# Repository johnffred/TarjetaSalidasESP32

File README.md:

# 🔌 Proyecto: Tarjeta de salidas con ESP32

Este proyecto consiste en el diseño y desarrollo de una tarjeta electrónica basada en ESP32, que permite controlar múltiples salidas mediante relés de estado sólido, visualizar información en una pantalla LCD y recibir entradas desde botones físicos. Todo el diseño de hardware se ha realizado en **KiCad**.

---

## 📦 Componentes principales

| Componente             | Descripción                                      |
|------------------------|--------------------------------------------------|
| ESP32-WROOM-32D        | Microcontrolador principal                       |
| Relés G3MB-202P        | Relés de estado sólido para controlar salidas    |
| Pantalla LCD 16x2 I2C  | Interfaz de usuario                              |
| Botones de entrada     | Para control manual de salidas                   |
| Fuente IRM-05-5        | Fuente de 5 V conmutada                           |
| CH340C                 | Conversor USB a serial para programar el ESP32   |
| USB Tipo A             | Conexión de energía o programación               |

---

## 📐 Diseño en KiCad

- `esquematico.kicad_sch`: esquema eléctrico completo
- `pcb_layout.kicad_pcb`: diseño de la placa (en desarrollo)
- `BOM.csv`: lista de materiales (opcional)

---

## 💻 Programación

La programación se realiza en Arduino IDE o PlatformIO.  
Funcionalidades previstas:
- Activación de salidas mediante botones
- Visualización del estado de salidas en la pantalla LCD
- Control de pines y lógica de relés

📌 Asignación de pines:

| Función     | Pin ESP32 |
|-------------|-----------|
| Relé 1      | GPIO25    |
| Relé 2      | GPIO26    |
| Relé 3      | GPIO27    |
| Relé 4      | GPIO32    |
| Botones     | GPIO34, 35, 36, 39 |
| LCD I2C SDA | GPIO21    |
| LCD I2C SCL | GPIO22    |

---

## 📋 Estado del proyecto

| Tarea                          | Estado     |
|-------------------------------|------------|
| Diseño de esquema             | ✅ Completo |
| Diseño PCB                    | ⏳ En progreso |
| Programación básica           | ⏳ En pruebas |
| Pruebas de relés              | 🔜 Por hacer |
| Documentación en GitHub       | ✅ Lista    |

---

## 🧑‍💻 Autor

**John Franco**  
📅 Junio 2025  
🔗 Licencia: MIT

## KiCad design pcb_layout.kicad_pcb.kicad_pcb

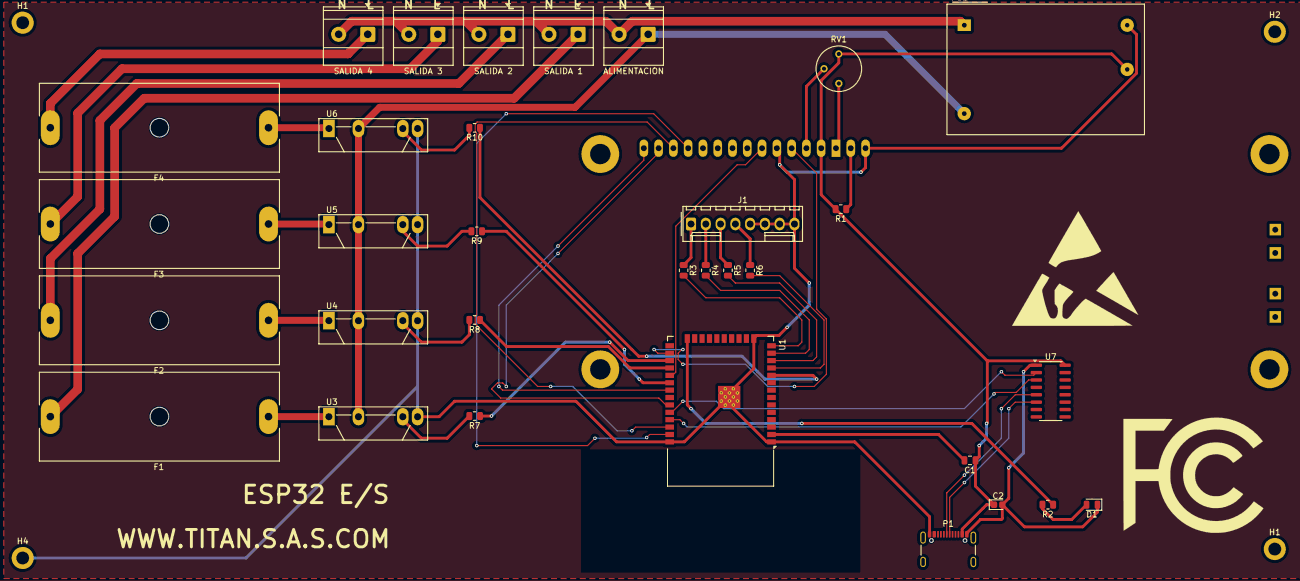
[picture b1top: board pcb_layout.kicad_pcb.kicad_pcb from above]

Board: 2 copper layers, 37 parts (1 on the bottom side), 43 nets.

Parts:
ALIMENTACION: alimentacion; TerminalBlock_Phoenix_MKDS-1,5-2_1x02_P5.00mm_Horizontal
C1: C100nF; C_0805_2012Metric
C2: C_Polarized; CP_EIA-1608-08_AVX-J
D1: LED; LED_0805_2012Metric
F1, F2, F3, F4: Fuse_Small; Fuseholder_Cylinder-6.3x32mm_Schurter_0031-8002_Horizontal_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
H1, H1#2, H2, H4: MountingHole_2.2mm_M2_DIN965_Pad
J1: Conn_01x08; Molex_KK-254_AE-6410-08A_1x08_P2.54mm_Vertical
P1: USB_C_Plug_USB2.0; USB_C_Receptacle_GCT_USB4105-xx-A_16P_TopMnt_Horizontal
PS1: IRM-02-5; Converter_ACDC_MeanWell_IRM-02-xx_THT
R1: R_US330ohn; R_0805_2012Metric
R2, R3, R4, R5, R6: R_US; R_0805_2012Metric
R7, R8, R9, R10: 330ohm; R_0805_2012Metric
RV1: R_Potentiometer_US; Potentiometer_Bourns_3339P_Vertical
SALIDA 1, SALIDA 2, SALIDA 3, SALIDA 4: salida; TerminalBlock_Phoenix_MKDS-1,5-2_1x02_P5.00mm_Horizontal
U1: ESP32-WROOM-32D
U2: LCD-016N002L
U3, U4, U5, U6: S202S02; SIP4_Sharp-SSR_P7.62mm_Straight
U7: CH340C; SOIC-16_3.9x9.9mm_P1.27mm

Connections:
IO01: U1.35 (TXD0/IO1), U7.3 (RXD)
IO03: U1.34 (RXD0/IO3), U7.2 (TXD)
IO4: U1.26 (IO4), U2.4 (RS)
IO5: U1.29 (IO5), U2.6 (E)
IO12: R3.2, U1.14 (IO12)
IO14: R4.2, U1.13 (IO14)
IO16: R7.1, U1.27 (IO16)
IO17: R8.1, U1.28 (IO17)
IO18: R9.1, U1.30 (IO18)
IO19: U1.31 (IO19), U2.14 (DB7)
IO21: U1.33 (IO21), U2.13 (DB6)
IO22: U1.36 (IO22), U2.12 (DB5)
IO23: U1.37 (IO23), U2.11 (DB4)
IO25: R10.1, U1.10 (IO25)
IO26: R6.2, U1.11 (IO26)
IO27: R5.2, U1.12 (IO27)
unnamed: D1.2 (A), R2.2
unnamed: F1.1, U3.1
unnamed: F2.1, U4.1
unnamed: F3.1, U5.1
unnamed: F4.1, U6.1
unnamed: J1.1, R3.1
unnamed: J1.2, R4.1
unnamed: J1.3, R5.1
unnamed: J1.4, R6.1
unnamed: F1.2, SALIDA 1.1
unnamed: F2.2, SALIDA 2.1
unnamed: F3.2, SALIDA 3.1
unnamed: F4.2, SALIDA 4.1
unnamed: P1.A6 (D+), U7.5 (UD+)
unnamed: P1.A7 (D-), U7.6 (UD-)
unnamed: R7.2, U3.3
unnamed: R8.2, U4.3
unnamed: R9.2, U5.3
unnamed: R10.2, U6.3
unnamed: R2.1, U1.24 (IO2)
unnamed: C1.2, U1.2 (VDD)
unnamed: R1.1, U2.15 (A/VEE)
unnamed: RV1.2, U2.3 (VO)
Neutro: ALIMENTACION.2, PS1.1 (AC/N), SALIDA 1.2, SALIDA 2.2, SALIDA 3.2, SALIDA 4.2
gnd: C2.2, D1.1 (K), H1.3, H1#2.1, H2.2, H4.4, J1.5, J1.6, J1.7, J1.8, P1.A1 (GND), P1.A12 (GND), P1.B1 (GND), P1.B12 (GND), PS1.3 (-Vo), RV1.1, U1.1 (GND), U1.15 (GND), U1.38 (GND), U1.39 (GND), U2.1 (VSS), U2.5 (R/~W), U2.16 (K), U3.4, U4.4, U5.4, U6.4, U7.1 (GND)
linea: ALIMENTACION.1, PS1.2 (AC/L), U3.2, U4.2, U5.2, U6.2
vcc: C1.1, C2.1, P1.A4 (VBUS), P1.A9 (VBUS), P1.B4 (VBUS), P1.B9 (VBUS), PS1.4 (+Vo), R1.2, RV1.3, U2.2 (VDD), U7.16 (VCC)

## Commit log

2025-06-25 README.md
